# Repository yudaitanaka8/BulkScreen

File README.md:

# BulkScreen

内容物  
Firmware(モーターの制御コード)  
PCB(基板データ)  
-回路・基盤画像(pdf)  
-gerberデータ  
  
Arduinoからの配線がわからなくなったら、PCBフォルダのimagesにある画像を見る。回路図のピンの並びと実際のピンの並びは一緒。

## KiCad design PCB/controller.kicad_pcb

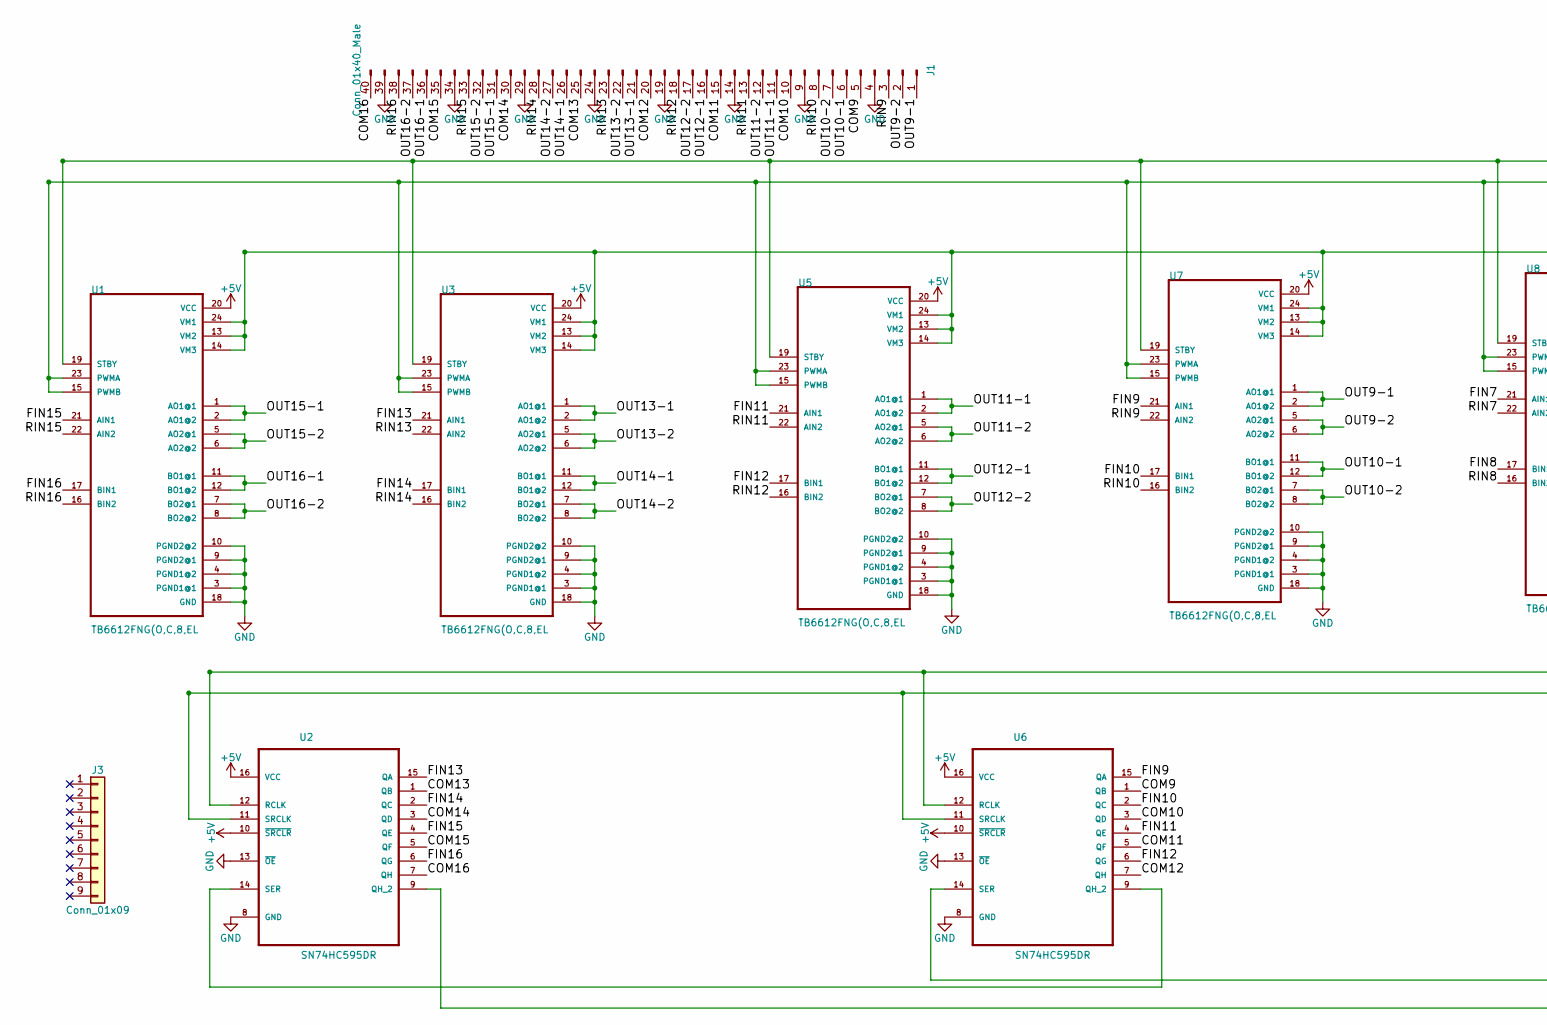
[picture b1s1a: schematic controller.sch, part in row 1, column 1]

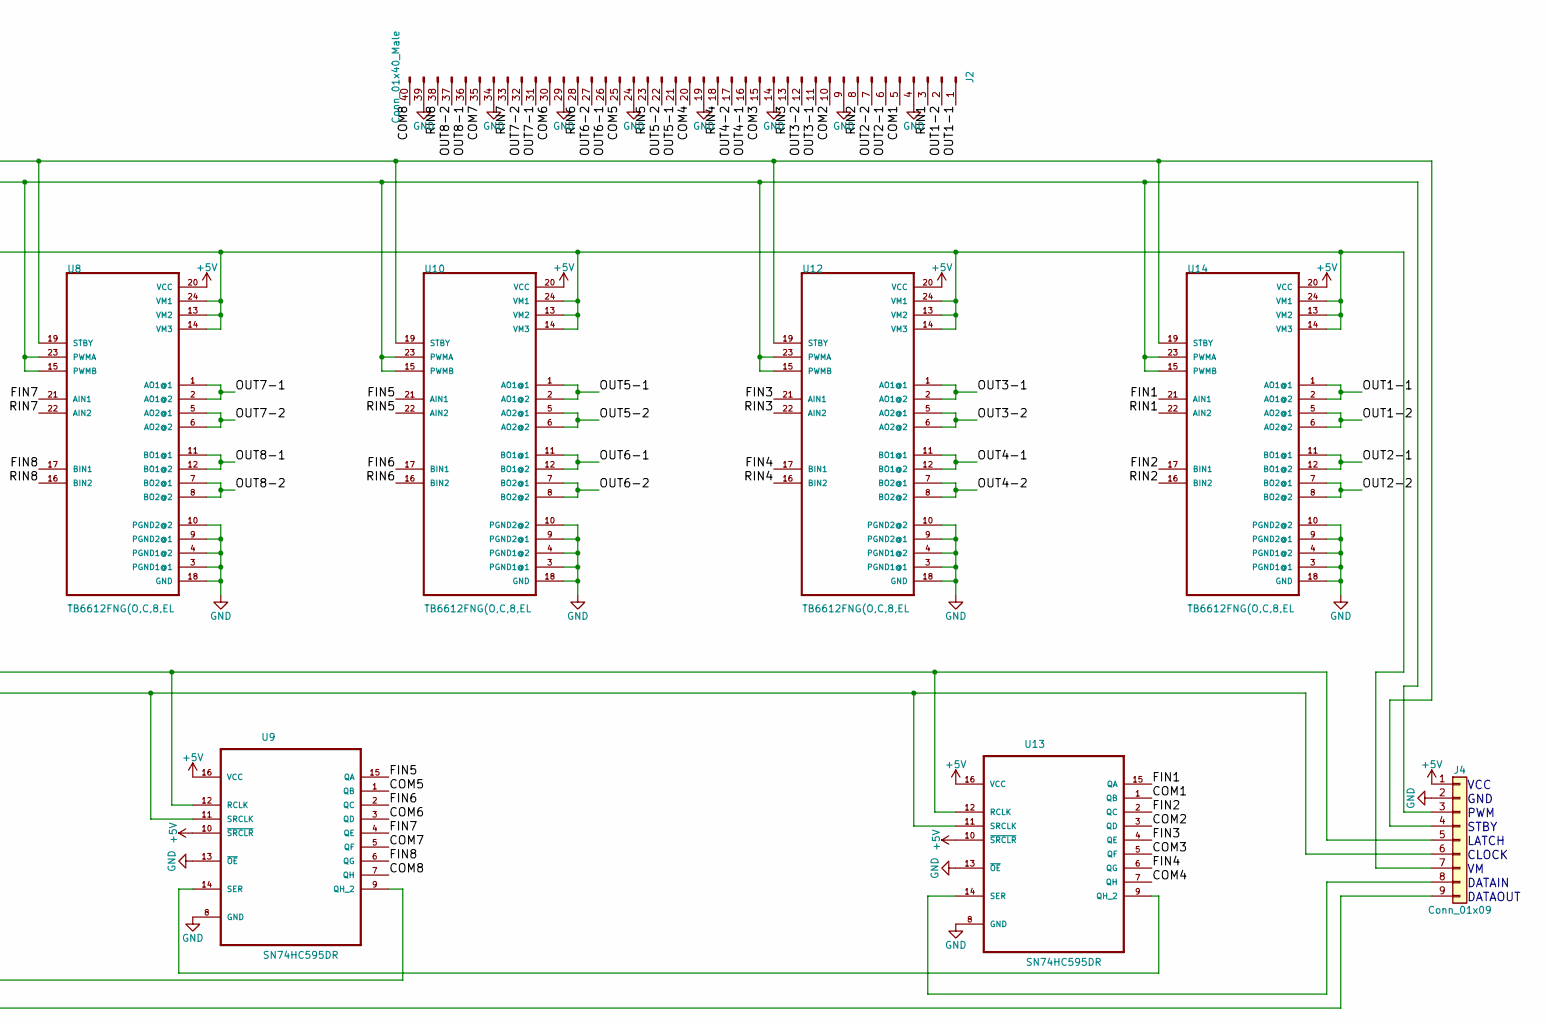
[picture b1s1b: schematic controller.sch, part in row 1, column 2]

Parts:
J1, J2: Conn_01x40_Male; Pin_Header_Straight_1x40_Pitch2.54mm
J3, J4: Conn_01x09; Pin_Header_Straight_1x09_Pitch2.54mm
U1, U3, U5, U7, U8, U10, U12, U14: TB6612FNG(O,C,8,EL; SSOP-24_5.3x8.2mm_Pitch0.65mm
U2, U6, U9, U13: SN74HC595DR; SOIC-16_3.9x9.9mm_Pitch1.27mm

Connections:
+5V: J4.1, U1.20 (VCC), U2.10 (~SRCLR), U2.16 (VCC), U3.20 (VCC), U5.20 (VCC), U6.10 (~SRCLR), U6.16 (VCC), U7.20 (VCC), U8.20 (VCC), U9.10 (~SRCLR), U9.16 (VCC), U10.20 (VCC), U12.20 (VCC), U13.10 (~SRCLR), U13.16 (VCC), U14.20 (VCC)
/COM1: J2.5, U13.1 (QB)
/COM2: J2.10, U13.3 (QD)
/COM3: J2.15, U13.5 (QF)
/COM4: J2.20, U13.7 (QH)
/COM5: J2.25, U9.1 (QB)
/COM6: J2.30, U9.3 (QD)
/COM7: J2.35, U9.5 (QF)
/COM8: J2.40, U9.7 (QH)
/COM9: J1.5, U6.1 (QB)
/COM10: J1.10, U6.3 (QD)
/COM11: J1.15, U6.5 (QF)
/COM12: J1.20, U6.7 (QH)
/COM13: J1.25, U2.1 (QB)
/COM14: J1.30, U2.3 (QD)
/COM15: J1.35, U2.5 (QF)
/COM16: J1.40, U2.7 (QH)
/FIN1: U13.15 (QA), U14.21 (AIN1)
/FIN2: U13.2 (QC), U14.17 (BIN1)
/FIN3: U12.21 (AIN1), U13.4 (QE)
/FIN4: U12.17 (BIN1), U13.6 (QG)
/FIN5: U9.15 (QA), U10.21 (AIN1)
/FIN6: U9.2 (QC), U10.17 (BIN1)
/FIN7: U8.21 (AIN1), U9.4 (QE)
/FIN8: U8.17 (BIN1), U9.6 (QG)
/FIN9: U6.15 (QA), U7.21 (AIN1)
/FIN10: U6.2 (QC), U7.17 (BIN1)
/FIN11: U5.21 (AIN1), U6.4 (QE)
/FIN12: U5.17 (BIN1), U6.6 (QG)
/FIN13: U2.15 (QA), U3.21 (AIN1)
/FIN14: U2.2 (QC), U3.17 (BIN1)
/FIN15: U1.21 (AIN1), U2.4 (QE)
/FIN16: U1.17 (BIN1), U2.6 (QG)
/OUT1-1: J2.1, U14.1 (AO1@1), U14.2 (AO1@2)
/OUT1-2: J2.2, U14.5 (AO2@1), U14.6 (AO2@2)
/OUT2-1: J2.6, U14.11 (BO1@1), U14.12 (BO1@2)
/OUT2-2: J2.7, U14.7 (BO2@1), U14.8 (BO2@2)
/OUT3-1: J2.11, U12.1 (AO1@1), U12.2 (AO1@2)
/OUT3-2: J2.12, U12.5 (AO2@1), U12.6 (AO2@2)
/OUT4-1: J2.16, U12.11 (BO1@1), U12.12 (BO1@2)
/OUT4-2: J2.17, U12.7 (BO2@1), U12.8 (BO2@2)
/OUT5-1: J2.21, U10.1 (AO1@1), U10.2 (AO1@2)
/OUT5-2: J2.22, U10.5 (AO2@1), U10.6 (AO2@2)
/OUT6-1: J2.26, U10.11 (BO1@1), U10.12 (BO1@2)
/OUT6-2: J2.27, U10.7 (BO2@1), U10.8 (BO2@2)
/OUT7-1: J2.31, U8.1 (AO1@1), U8.2 (AO1@2)
/OUT7-2: J2.32, U8.5 (AO2@1), U8.6 (AO2@2)
/OUT8-1: J2.36, U8.11 (BO1@1), U8.12 (BO1@2)
/OUT8-2: J2.37, U8.7 (BO2@1), U8.8 (BO2@2)
/OUT9-1: J1.1, U7.1 (AO1@1), U7.2 (AO1@2)
/OUT9-2: J1.2, U7.5 (AO2@1), U7.6 (AO2@2)
/OUT10-1: J1.6, U7.11 (BO1@1), U7.12 (BO1@2)
/OUT10-2: J1.7, U7.7 (BO2@1), U7.8 (BO2@2)
/OUT11-1: J1.11, U5.1 (AO1@1), U5.2 (AO1@2)
/OUT11-2: J1.12, U5.5 (AO2@1), U5.6 (AO2@2)
/OUT12-1: J1.16, U5.11 (BO1@1), U5.12 (BO1@2)
/OUT12-2: J1.17, U5.7 (BO2@1), U5.8 (BO2@2)
/OUT13-1: J1.21, U3.1 (AO1@1), U3.2 (AO1@2)
/OUT13-2: J1.22, U3.5 (AO2@1), U3.6 (AO2@2)
/OUT14-1: J1.26, U3.11 (BO1@1), U3.12 (BO1@2)
/OUT14-2: J1.27, U3.7 (BO2@1), U3.8 (BO2@2)
/OUT15-1: J1.31, U1.1 (AO1@1), U1.2 (AO1@2)
/OUT15-2: J1.32, U1.5 (AO2@1), U1.6 (AO2@2)
/OUT16-1: J1.36, U1.11 (BO1@1), U1.12 (BO1@2)
/OUT16-2: J1.37, U1.7 (BO2@1), U1.8 (BO2@2)
/RIN1: J2.3, U14.22 (AIN2)
/RIN2: J2.8, U14.16 (BIN2)
/RIN3: J2.13, U12.22 (AIN2)
/RIN4: J2.18, U12.16 (BIN2)
/RIN5: J2.23, U10.22 (AIN2)
/RIN6: J2.28, U10.16 (BIN2)
/RIN7: J2.33, U8.22 (AIN2)
/RIN8: J2.38, U8.16 (BIN2)
/RIN9: J1.3, U7.22 (AIN2)
/RIN10: J1.8, U7.16 (BIN2)
/RIN11: J1.13, U5.22 (AIN2)
/RIN12: J1.18, U5.16 (BIN2)
/RIN13: J1.23, U3.22 (AIN2)
/RIN14: J1.28, U3.16 (BIN2)
/RIN15: J1.33, U1.22 (AIN2)
/RIN16: J1.38, U1.16 (BIN2)
GND: J1.4, J1.9, J1.14, J1.19, J1.24, J1.29, J1.34, J1.39, J2.4, J2.9, J2.14, J2.19, J2.24, J2.29, J2.34, J2.39, J4.2, U1.3 (PGND1@1), U1.4 (PGND1@2), U1.9 (PGND2@1), U1.10 (PGND2@2), U1.18 (GND), U2.8 (GND), U2.13 (~OE), U3.3 (PGND1@1), U3.4 (PGND1@2), U3.9 (PGND2@1), U3.10 (PGND2@2), U3.18 (GND), U5.3 (PGND1@1), U5.4 (PGND1@2), U5.9 (PGND2@1), U5.10 (PGND2@2), U5.18 (GND), U6.8 (GND), U6.13 (~OE), U7.3 (PGND1@1), U7.4 (PGND1@2), U7.9 (PGND2@1), U7.10 (PGND2@2), U7.18 (GND), U8.3 (PGND1@1), U8.4 (PGND1@2), U8.9 (PGND2@1), U8.10 (PGND2@2), U8.18 (GND), U9.8 (GND), U9.13 (~OE), U10.3 (PGND1@1), U10.4 (PGND1@2), U10.9 (PGND2@1), U10.10 (PGND2@2), U10.18 (GND), U12.3 (PGND1@1), U12.4 (PGND1@2), U12.9 (PGND2@1), U12.10 (PGND2@2), U12.18 (GND), U13.8 (GND), U13.13 (~OE), U14.3 (PGND1@1), U14.4 (PGND1@2), U14.9 (PGND2@1), U14.10 (PGND2@2), U14.18 (GND)
unnamed: J4.3, U1.15 (PWMB), U1.23 (PWMA), U3.15 (PWMB), U3.23 (PWMA), U5.15 (PWMB), U5.23 (PWMA), U7.15 (PWMB), U7.23 (PWMA), U8.15 (PWMB), U8.23 (PWMA), U10.15 (PWMB), U10.23 (PWMA), U12.15 (PWMB), U12.23 (PWMA), U14.15 (PWMB), U14.23 (PWMA)
unnamed: J4.4, U1.19 (STBY), U3.19 (STBY), U5.19 (STBY), U7.19 (STBY), U8.19 (STBY), U10.19 (STBY), U12.19 (STBY), U14.19 (STBY)
unnamed: J4.5, U2.12 (RCLK), U6.12 (RCLK), U9.12 (RCLK), U13.12 (RCLK)
unnamed: J4.6, U2.11 (SRCLK), U6.11 (SRCLK), U9.11 (SRCLK), U13.11 (SRCLK)
unnamed: J4.7, U1.13 (VM2), U1.14 (VM3), U1.24 (VM1), U3.13 (VM2), U3.14 (VM3), U3.24 (VM1), U5.13 (VM2), U5.14 (VM3), U5.24 (VM1), U7.13 (VM2), U7.14 (VM3), U7.24 (VM1), U8.13 (VM2), U8.14 (VM3), U8.24 (VM1), U10.13 (VM2), U10.14 (VM3), U10.24 (VM1), U12.13 (VM2), U12.14 (VM3), U12.24 (VM1), U14.13 (VM2), U14.14 (VM3), U14.24 (VM1)
unnamed: J4.8, U13.14 (SER)
unnamed: J4.9, U2.9 (QH_2)
unnamed: U2.14 (SER), U6.9 (QH_2)
unnamed: U6.14 (SER), U9.9 (QH_2)
unnamed: U9.14 (SER), U13.9 (QH_2)

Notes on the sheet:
VCC
GND
PWM
STBY
LATCH
CLOCK
DATAIN
DATAOUT

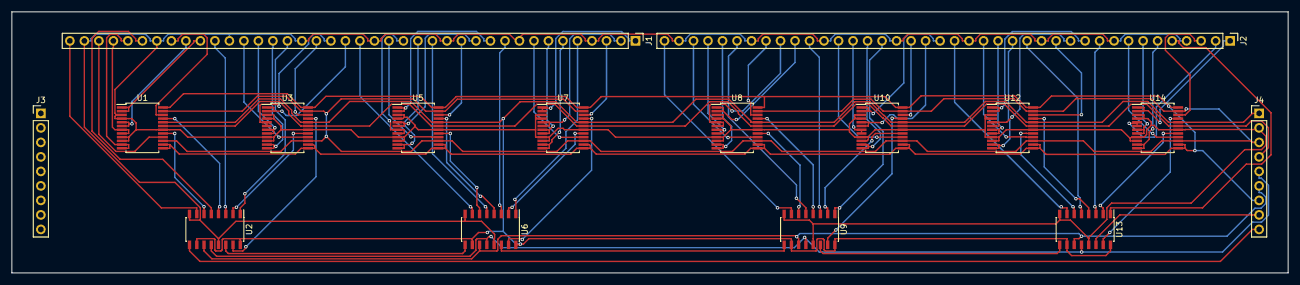
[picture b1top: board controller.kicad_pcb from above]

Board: 2 copper layers, 223.5 x 45.7 mm, 16 parts (0 on the bottom side), 92 nets.

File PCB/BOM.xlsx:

部品番号(Designator) | 品名(Name)ヒンメイ | 個数(Quantity)コスウ | パッケージ(Package) | 部品メーカー(Manufacturer)ー | 品番(Manufacturer Part Number)ヒンバン
J1,J2 | ピンヘッダ | 2
J3,J4 | ピンヘッダ | 2
U1,U3,U5,U7,U8,U10,U12,U14 | モータードライバー | 8 | SSOP-24_5.3x8.2mm_Pitch0.65mm | TOSHIBA | TB6612FNG
U2,U6,U9,U13 | シフトレジスター | 4 | SOIC-16_3.9x9.9mm_Pitch1.27mm | Texas Instruments | SN74HC595DR

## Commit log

2019-01-15 add new file
2019-01-28 move all motors at the same time
2019-01-31 function move_motor
2019-02-01 move each motor according to test_array
2019-02-03 control the direction of rotation
